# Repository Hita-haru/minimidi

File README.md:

# Little mini midi
## Description of this project.
This is my first midi keyboard.  
I used to https://blueprint.hackclub.com/starter-projects/midi as a reference.  

I was thinking I wish I could making songs with midi keyboard that graphical and useful.
So I maked this midi keyboard.

## Screenshots
Schematic  
  
PCB(Layout)  
  
PCB(Final version)  
  
Programming  
  
## Estimates
JLCPCB Estimate  
  
LCSC Estimate  

## BOM
|Name           |Quantity|
|---------------|--------|
|Cherry MX Key  |35      |
|PinHeader 1x08 |1       |
|Diode          |36      |
|RotaryEncoder  |2       |
|RP Pi Pico     |1       |
|PinHeader 1x20 |2       |

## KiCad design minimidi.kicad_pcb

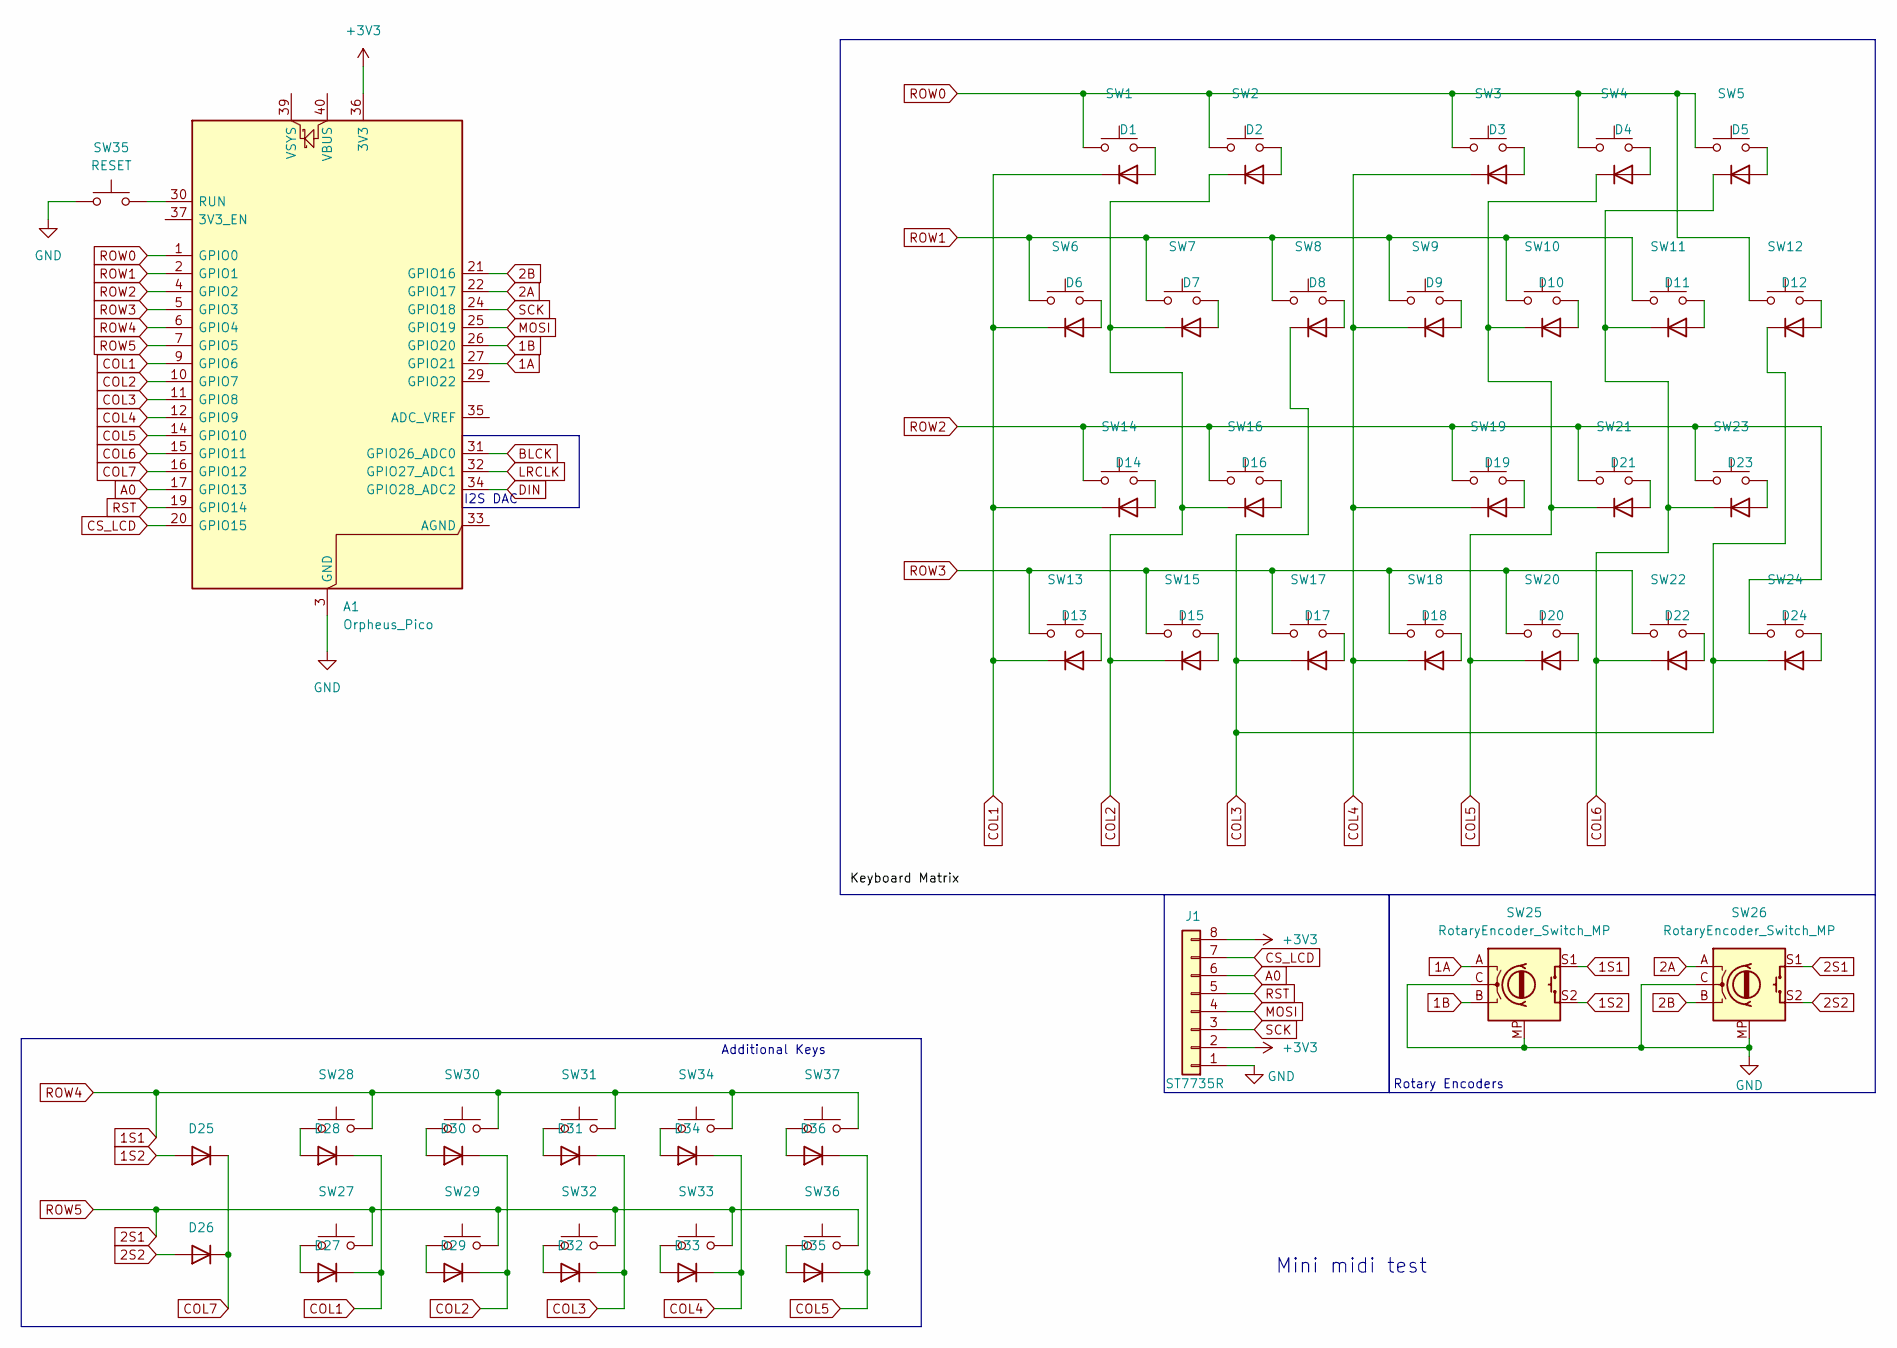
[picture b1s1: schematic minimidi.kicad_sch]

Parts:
A1: Orpheus_Pico; RaspberryPi_Pico_Common_THT
D1, D2, D3, D4, D5, D6, D7, D8, D9, D10, D11, D12, D13, D14, D15, D16, D17, D18, D19, D20, D21, D22, D23, D24, D25, D26, D27, D28, D29, D30, D31, D32, D33, D34, D35, D36: 1N4148WT; D_SOD-523
J1: ST7735R; PinHeader_1x08_P2.54mm_Vertical
SW1, SW2, SW3, SW4, SW5, SW6, SW7, SW8, SW9, SW10, SW11, SW12, SW13, SW14, SW15, SW16, SW17, SW18, SW19, SW20, SW21, SW22, SW23, SW24, SW27, SW28, SW29, SW30, SW31, SW32, SW33, SW34, SW36, SW37: SW_Push; SW_Cherry_MX_1.00u_PCB
SW25, SW26: RotaryEncoder_Switch_MP; RotaryEncoder_Alps_EC11E-Switch_Vertical_H20mm_MountingHoles
SW35: RESET; SW_Cherry_MX_1.00u_PCB

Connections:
1A: A1.27 (GPIO21), SW25.A
1B: A1.26 (GPIO20), SW25.B
1S1: A1.6 (GPIO4), SW25.S1, SW28.2, SW30.2, SW31.2, SW34.2, SW37.2
1S2: D25.2 (A), SW25.S2
2A: A1.22 (GPIO17), SW26.A
2B: A1.21 (GPIO16), SW26.B
2S1: A1.7 (GPIO5), SW26.S1, SW27.2, SW29.2, SW32.2, SW33.2, SW36.2
2S2: D26.2 (A), SW26.S2
+3V3: A1.36 (3V3), J1.2, J1.8
A0: A1.17 (GPIO13), J1.6
BLCK: A1.31 (GPIO26_ADC0)
COL1: A1.9 (GPIO6), D1.1 (K), D6.1 (K), D13.1 (K), D14.1 (K), D27.1 (K), D28.1 (K)
COL2: A1.10 (GPIO7), D2.1 (K), D7.1 (K), D15.1 (K), D16.1 (K), D29.1 (K), D30.1 (K)
COL3: A1.11 (GPIO8), D8.1 (K), D12.1 (K), D17.1 (K), D24.1 (K), D31.1 (K), D32.1 (K)
COL4: A1.12 (GPIO9), D3.1 (K), D9.1 (K), D18.1 (K), D19.1 (K), D33.1 (K), D34.1 (K)
COL5: A1.14 (GPIO10), D4.1 (K), D10.1 (K), D20.1 (K), D21.1 (K), D35.1 (K), D36.1 (K)
COL6: A1.15 (GPIO11), D5.1 (K), D11.1 (K), D22.1 (K), D23.1 (K)
COL7: A1.16 (GPIO12), D25.1 (K), D26.1 (K)
CS_LCD: A1.20 (GPIO15), J1.7
DIN: A1.34 (GPIO28_ADC2)
GND: A1.3 (GND), A1.8 (GND), A1.13 (GND), A1.18 (GND), A1.23 (GND), A1.28 (GND), A1.38 (GND), J1.1, SW25.C, SW25.MP, SW26.C, SW26.MP, SW35.1
LRCLK: A1.32 (GPIO27_ADC1)
MOSI: A1.25 (GPIO19), J1.4
unnamed: A1.30 (RUN), SW35.2
unnamed: D1.2 (A), SW1.2
unnamed: D2.2 (A), SW2.2
unnamed: D3.2 (A), SW3.2
unnamed: D4.2 (A), SW4.2
unnamed: D5.2 (A), SW5.2
unnamed: D6.2 (A), SW6.2
unnamed: D7.2 (A), SW7.2
unnamed: D8.2 (A), SW8.2
unnamed: D9.2 (A), SW9.2
unnamed: D10.2 (A), SW10.2
unnamed: D11.2 (A), SW11.2
unnamed: D12.2 (A), SW12.2
unnamed: D13.2 (A), SW13.2
unnamed: D14.2 (A), SW14.2
unnamed: D15.2 (A), SW15.2
unnamed: D16.2 (A), SW16.2
unnamed: D17.2 (A), SW17.2
unnamed: D18.2 (A), SW18.2
unnamed: D19.2 (A), SW19.2
unnamed: D20.2 (A), SW20.2
unnamed: D21.2 (A), SW21.2
unnamed: D22.2 (A), SW22.2
unnamed: D23.2 (A), SW23.2
unnamed: D24.2 (A), SW24.2
unnamed: D27.2 (A), SW27.1
unnamed: D28.2 (A), SW28.1
unnamed: D29.2 (A), SW29.1
unnamed: D30.2 (A), SW30.1
unnamed: D31.2 (A), SW31.1
unnamed: D32.2 (A), SW32.1
unnamed: D33.2 (A), SW33.1
unnamed: D34.2 (A), SW34.1
unnamed: D35.2 (A), SW36.1
unnamed: D36.2 (A), SW37.1
ROW0: A1.1 (GPIO0), SW1.1, SW2.1, SW3.1, SW4.1, SW5.1, SW12.1
ROW1: A1.2 (GPIO1), SW6.1, SW7.1, SW8.1, SW9.1, SW10.1, SW11.1
ROW2: A1.4 (GPIO2), SW14.1, SW16.1, SW19.1, SW21.1, SW23.1, SW24.1
ROW3: A1.5 (GPIO3), SW13.1, SW15.1, SW17.1, SW18.1, SW20.1, SW22.1
RST: A1.19 (GPIO14), J1.5
SCK: A1.24 (GPIO18), J1.3

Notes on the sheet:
Mini midi test
I2S DAC
Additional Keys
Rotary Encoders

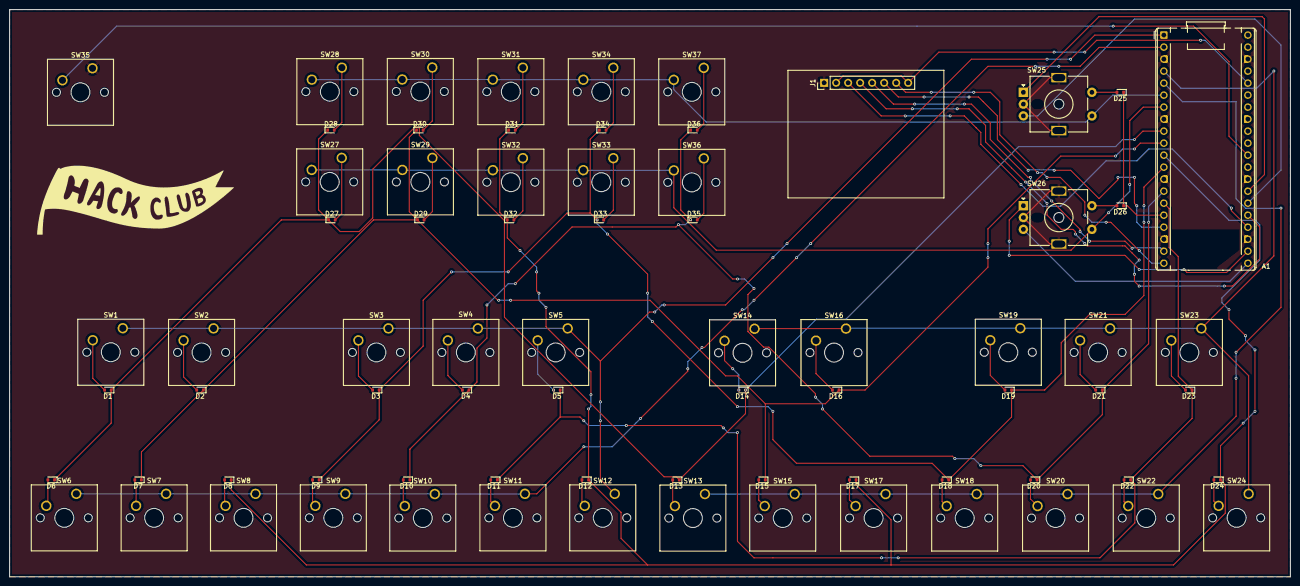
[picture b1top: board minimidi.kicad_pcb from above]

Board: 2 copper layers, 271.0 x 120.0 mm, 75 parts (0 on the bottom side), 61 nets.

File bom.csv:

"ID";"指定子";"フットプリント";"数量";"名称";"供給業者、参考資料";
1;"SW28,SW33,SW24,SW13,SW32,SW12,SW31,SW19,SW20,SW30,SW23,SW16,SW17,SW6,SW21,SW27,SW10,SW3,SW34,SW14,SW11,SW36,SW18,SW1,SW8,SW9,SW15,SW7,SW22,SW5,SW37,SW4,SW2,SW29";"SW_Cherry_MX_1.00u_PCB";34;"SW_Push";;;
2;"D21,D3,D22,D29,D35,D5,D25,D15,D17,D30,D24,D4,D34,D26,D19,D6,D36,D10,D28,D2,D12,D20,D31,D23,D18,D33,D32,D11,D13,D9,D14,D27,D16,D8,D1,D7";"D_SOD-523";36;"1N4148WT";;;
3;"SW25,SW26";"RotaryEncoder_Alps_EC11E-Switch_Vertical_H20mm_MountingHoles";2;"RotaryEncoder_Switch_MP";;;
4;"J1";"PinHeader_1x08_P2.54mm_Vertical";1;"ST7735R";;;
5;"SW35";"SW_Cherry_MX_1.00u_PCB";1;"RESET";;;
6;"A1";"RaspberryPi_Pico_Common_THT";1;"Orpheus_Pico";;;

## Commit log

2025-12-16 Making filesystems
2025-12-16 Making PCBs
2025-12-18 Making firmware
2025-12-18 Add screenshots
2025-12-18 Updating screenshots
2025-12-19 Updating README.md
